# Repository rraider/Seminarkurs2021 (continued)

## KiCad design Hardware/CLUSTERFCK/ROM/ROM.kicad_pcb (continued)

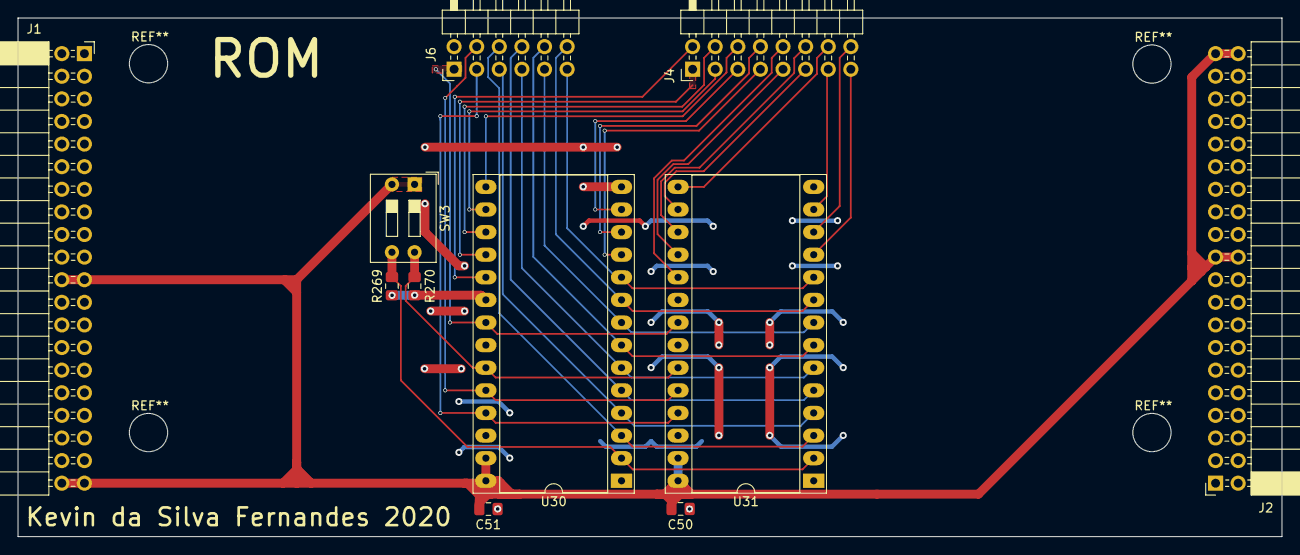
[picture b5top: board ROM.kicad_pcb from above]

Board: 2 copper layers, 142.0 x 58.3 mm, 11 parts (0 on the bottom side), 31 nets.
